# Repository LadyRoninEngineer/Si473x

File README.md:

# Si473x
Data Supporting development of Si473x series radios

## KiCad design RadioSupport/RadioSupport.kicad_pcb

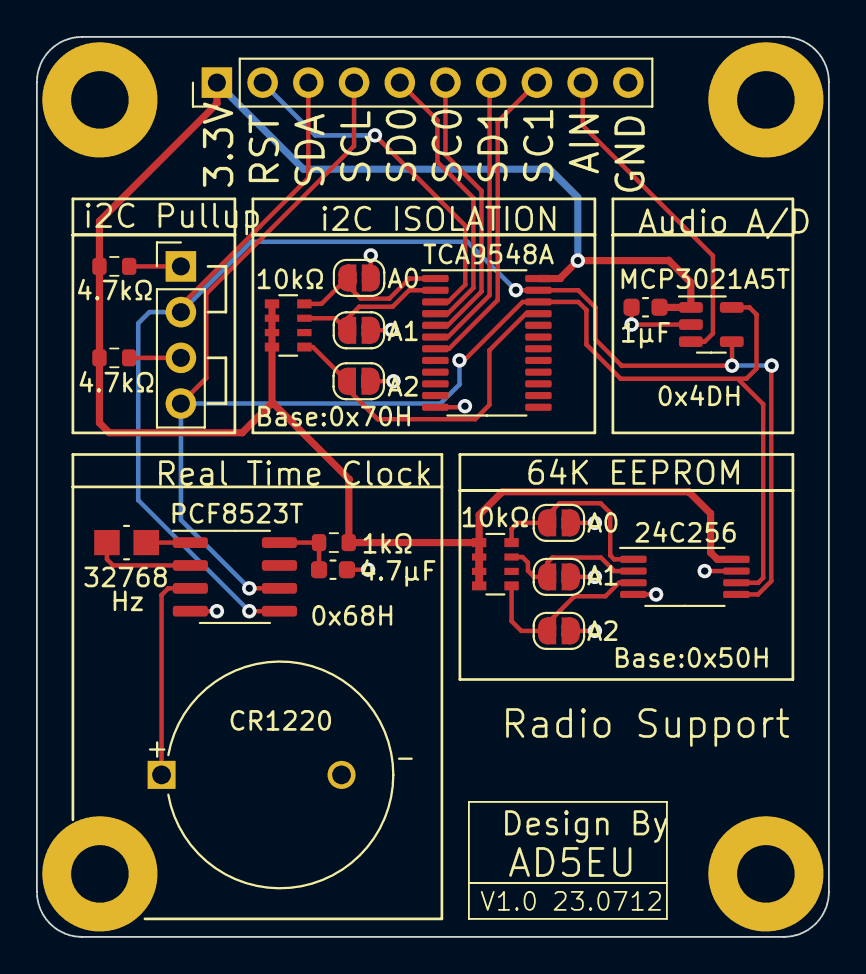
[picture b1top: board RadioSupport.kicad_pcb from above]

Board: 2 copper layers, 44.0 x 50.0 mm, 21 parts (0 on the bottom side), 22 nets.

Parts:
BT2: CR1220; BAT_BR1225A_HBN
C1: 4.7µF; C_0603_1608Metric
C2: 1µF; C_0603_1608Metric
J1: Conn_01x10_Pin; PinHeader_1x10_P2.54mm_Vertical
J2: Conn_01x04_Pin; PinHeader_1x04_P2.54mm_Vertical
JP1, JP2, JP3, JP4, JP5, JP6: Jumper_2_Bridged; SolderJumper-2_P1.3mm_Open_RoundedPad1.0x1.5mm
R1, R2: 4.7kΩ; R_0603_1608Metric
R3: 1kΩ; R_0603_1608Metric
RN1, RN2: 10kΩ; R_Array_Convex_4x0603
U1: TCA9548A; TSSOP-24_4.4x7.8mm_P0.65mm
U2: PCF8523T; SOIC-8_3.9x4.9mm_P1.27mm
U4: MCP3021A5T; SOT-23-5
U5: 24C256; TSSOP-8_4.4x3mm_P0.65mm
Y1: 32768; RT3215-32.768-12.5-TR

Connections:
+3.3V: C2.2, J1.1, R1.2, R2.2, R3.2, RN1.1 (R1.1), RN1.2 (R2.1), RN1.3 (R3.1), RN1.4 (R4.1), RN2.1 (R1.1), RN2.2 (R2.1), RN2.3 (R3.1), RN2.4 (R4.1), U1.24 (VCC), U4.1 (VDD), U5.8 (VCC)
AUDIO: J1.9, U4.3 (AIN)
GND: BT2.2 (-), C1.2, C2.1, J1.10, JP1.2 (B), JP2.2 (B), JP3.2 (B), JP4.2 (B), JP5.2 (B), JP6.2 (B), U1.12 (GND), U2.4 (VSS), U4.2 (VSS), U5.4 (GND), U5.7 (WP)
unnamed: BT2.1 (+), U2.3 (VBAT)
unnamed: J2.1, R2.1
unnamed: J2.3, R1.1
unnamed: JP1.1 (A), RN1.8 (R1.2), U1.1 (A0)
unnamed: JP2.1 (A), RN1.7 (R2.2), U1.2 (A1)
unnamed: JP3.1 (A), RN1.5 (R4.2), U1.21 (A2)
unnamed: JP4.1 (A), RN2.5 (R4.2), U5.3 (A2)
unnamed: JP5.1 (A), RN2.7 (R2.2), U5.2 (A1)
unnamed: JP6.1 (A), RN2.8 (R1.2), U5.1 (A0)
unnamed: U2.1 (OSCI), Y1.1
unnamed: U2.2 (OSCO), Y1.2
unnamed: C1.1, R3.1, U2.8 (VDD)
SCL: J1.4, J2.4, U1.22 (SCL), U2.6 (SCL), U4.5 (SCL), U5.6 (SCL)
SCL0: J1.6, U1.5 (SC0)
SCL1: J1.8, U1.7 (SC1)
SDA: J1.3, J2.2, U1.23 (SDA), U2.5 (SDA), U4.4 (SDA), U5.5 (SDA)
SDA0: J1.5, U1.4 (SD0)
SDA1: J1.7, U1.6 (SD1)
~RST: J1.2, U1.3 (~RESET)

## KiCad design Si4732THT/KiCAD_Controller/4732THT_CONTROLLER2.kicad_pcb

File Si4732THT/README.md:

Si4732 Through Hole Technology Radio
Developed By Nancy Gail Daniels - AD5EU

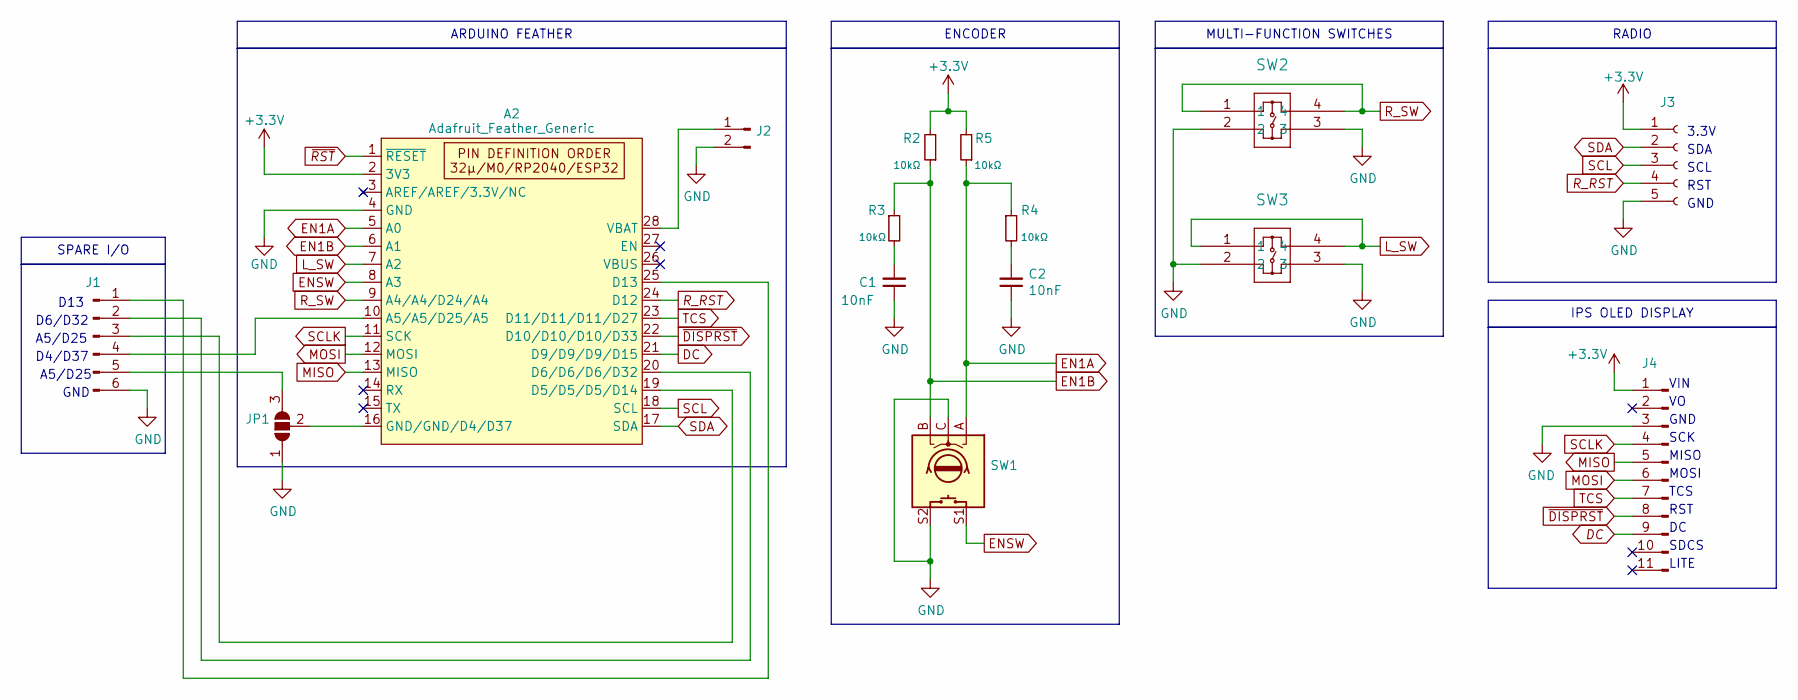
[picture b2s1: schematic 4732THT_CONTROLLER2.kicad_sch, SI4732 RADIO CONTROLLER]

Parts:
A2: Adafruit_Feather_Generic; Adafruit_Feather_WithMountingHoles
C1, C2: 10nF; C_Disc_D3.0mm_W1.6mm_P2.50mm; Mfr # C315C103K5R5TA; Digikey 399-4148-ND
J1: Conn_01x06_Pin; PinHeader_1x06_P2.54mm_Vertical
J2: Conn_01x02_Pin; JST_PH_S2B-PH-K_1x02_P2.00mm_Horizontal
J3: Conn_01x05_Socket; PinSocket_1x05_P2.54mm_Vertical
J4: Conn_01x11_Male; Display
JP1: SolderJumper_3_Open; SolderJumper-3_P1.3mm_Open_RoundedPad1.0x1.5mm
R2: 10kΩ; R_Axial_DIN0207_L6.3mm_D2.5mm_P7.62mm_Horizontal; Mfr # CFR-25JR-52-10K
R3, R4: 10kΩ; R_Axial_DIN0207_L6.3mm_D2.5mm_P7.62mm_Horizontal; Mfr # CFR-25JR-52-10K; Digikey 3-CFR-25JR-52-10KCT-ND
R5: 10kΩ; R_Axial_DIN0207_L6.3mm_D2.5mm_P7.62mm_Horizontal; Mfr # CFR-25JR-52-10K; Digikey 13-CFR-25JR-52-10KCT-ND
SW1: RotaryEncoder_Switch; RotaryEncoder_Alps_EC11E-Switch_Vertical_H20mm
SW2, SW3: D6R90F1LFS; D6R_CNK; Mfr # D6R90 F1 LFS; Digikey 401-1978-ND

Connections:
+3.3V: A2.2 (3V3), J3.1, J4.1, R2.2, R5.2
DC: A2.21 (D9/D9/D9/D15), J4.9
EN1A: A2.5 (A0), R4.1, R5.1, SW1.A
EN1B: A2.6 (A1), R2.1, R3.1, SW1.B
ENSW: A2.8 (A3), SW1.S1
GND: A2.4 (GND), C1.1, C2.1, J1.6, J2.2, J3.5, J4.3, JP1.1 (A), SW1.C, SW1.S2, SW2.2, SW2.3, SW3.2, SW3.3
L_SW: A2.7 (A2), SW3.1, SW3.4
MISO: A2.13 (MISO), J4.5
MOSI: A2.12 (MOSI), J4.6
unnamed: A2.10 (A5/A5/D25/A5), J1.4
unnamed: A2.19 (D5/D5/D5/D14), J1.3
unnamed: A2.20 (D6/D6/D6/D32), J1.2
unnamed: A2.25 (D13), J1.1
unnamed: A2.16 (GND/GND/D4/D37), JP1.2 (C)
unnamed: A2.28 (VBAT), J2.1
unnamed: C1.2, R3.2
unnamed: C2.2, R4.2
unnamed: J1.5, JP1.3 (B)
R_RST: A2.24 (D12), J3.4
R_SW: A2.9 (A4/A4/D24/A4), SW2.1, SW2.4
SCL: A2.18 (SCL), J3.3
SCLK: A2.11 (SCK), J4.4
SDA: A2.17 (SDA), J3.2
TCS: A2.23 (D11/D11/D11/D27), J4.7
~DISPRST: A2.22 (D10/D10/D10/D33), J4.8
~RST: A2.1 (~RESET)

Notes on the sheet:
RADIO
IPS OLED DISPLAY
MULTI-FUNCTION SWITCHES
ARDUINO FEATHER
SPARE I/O
ENCODER
SCL
SDCS
SDA
SCK
A5/D25
RST
VIN
TCS
LITE
MISO
MOSI
GND
3.3V
D4/D37
D6/D32
D13

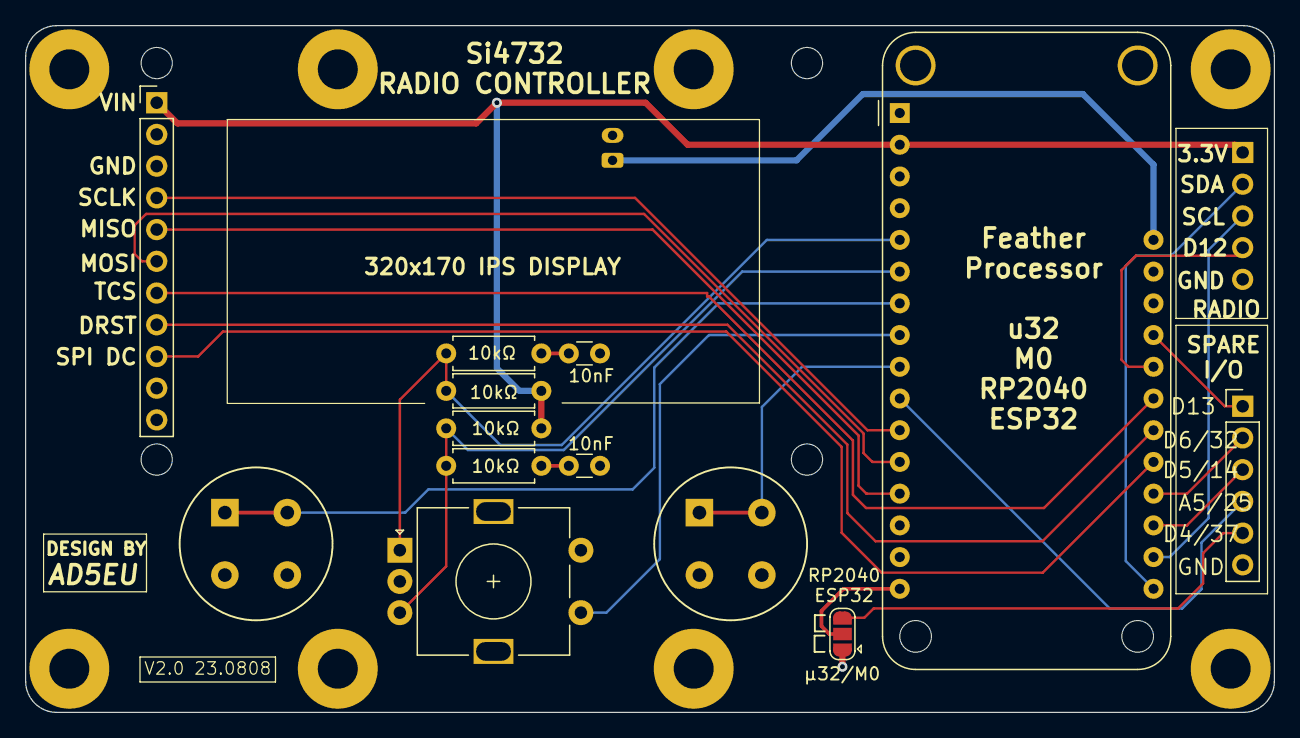
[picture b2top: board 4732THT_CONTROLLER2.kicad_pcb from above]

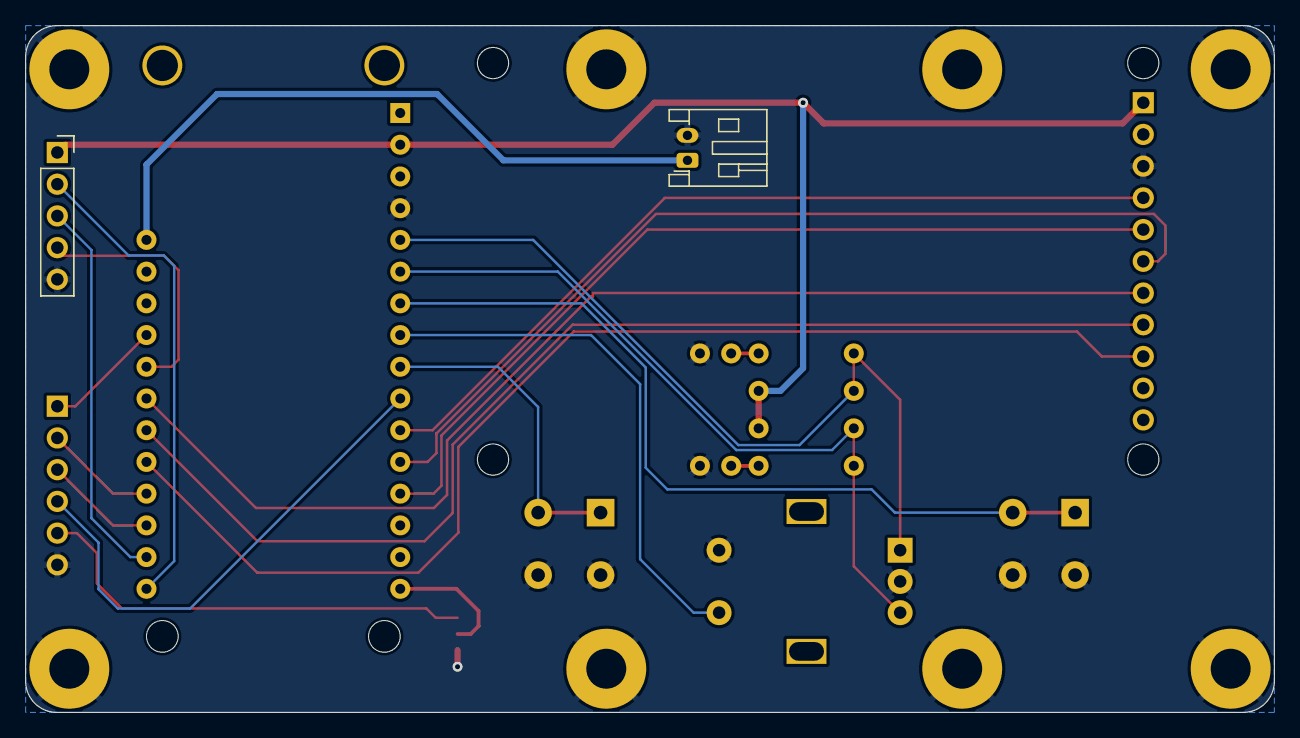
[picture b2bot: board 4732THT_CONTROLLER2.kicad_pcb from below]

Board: 2 copper layers, 100.0 x 55.0 mm, 15 parts (2 on the bottom side), 25 nets.

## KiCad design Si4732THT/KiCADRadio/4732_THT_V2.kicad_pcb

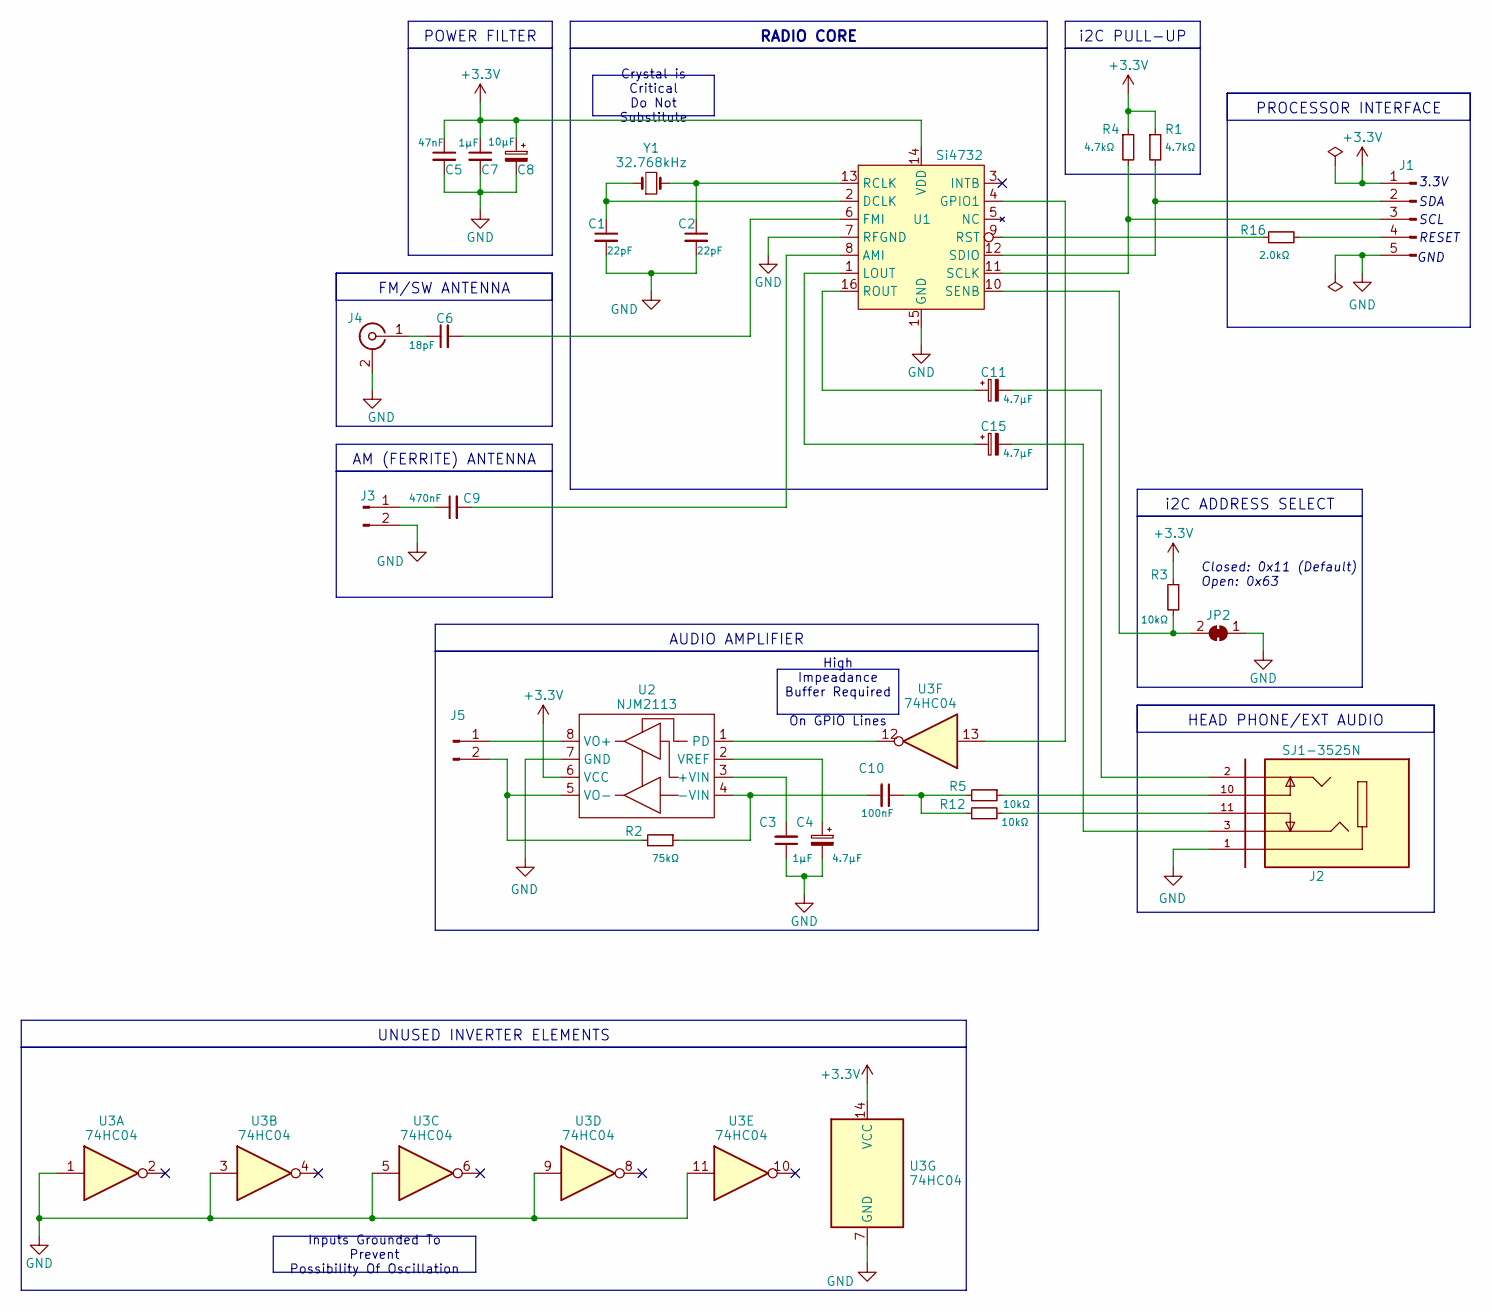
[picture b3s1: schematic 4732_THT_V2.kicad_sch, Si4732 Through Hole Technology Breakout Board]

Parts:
C1, C2: 22pF; C_Disc_D3.8mm_W2.6mm_P2.50mm
C3, C7: 1µF; CAP_C410C_AX_X7R_AXIMAX_KEM
C4, C11, C15: 4.7µF; CAPPRD250W45D400H500
C5: 47nF; C_Disc_D3.8mm_W2.6mm_P2.50mm
C6: 18pF; C_Disc_D3.8mm_W2.6mm_P2.50mm
C8: 10µF; CP_Radial_D4.0mm_P1.50mm
C9: 470nF; C_Disc_D3.8mm_W2.6mm_P2.50mm
C10: 100nF; C_Disc_D3.8mm_W2.6mm_P2.50mm
J1: Conn_01x05_Pin; PinHeader_1x05_P2.54mm_Vertical
J2: SJ1-3525N; CUI_SJ1-3525N; PARTREV 1.02
J3, J5: Conn_01x02_Pin; 1725656
J4: Conn_01x01_Female; SMA_Molex_73251-1153_EdgeMount_Horizontal
JP2: SolderJumper_2_Open; SolderJumper-2_P1.3mm_Bridged_RoundedPad1.0x1.5mm
R1, R4: 4.7kΩ; R_Axial_DIN0207_L6.3mm_D2.5mm_P7.62mm_Horizontal
R2: 75kΩ; R_Axial_DIN0207_L6.3mm_D2.5mm_P7.62mm_Horizontal
R3, R5, R12: 10kΩ; R_Axial_DIN0207_L6.3mm_D2.5mm_P7.62mm_Horizontal
R16: 2.0kΩ; R_Axial_DIN0207_L6.3mm_D2.5mm_P7.62mm_Horizontal
U1: Si4732; SOIC-16_3.9x9.9mm_P1.27mm
U2: NJM2113; DIP-8_W7.62mm
U3: 74HC04; DIP-14_W7.62mm
Y1: 32.768kHz; XTAL_ECS-.327-12.5-8X-C; Tolerance 20ppm; Mfr # ECS-.327-12.5-8X; Digikey X1123-ND

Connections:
+3.3V: C5.1, C7.1, C8.1, J1.1, R1.1, R3.1, R4.1, U1.14 (VDD), U2.6 (VCC), U3.14 (VCC)
GND: C1.2, C2.2, C3.1, C4.2, C5.2, C7.2, C8.2, J1.5, J2.1, J3.2, J4.2 (Ext), JP2.1 (A), U1.7 (RFGND), U1.15 (GND), U2.7 (GND), U3.1, U3.3, U3.5, U3.7 (GND), U3.9, U3.11
unnamed: C10.1, R5.2, R12.1
unnamed: C11.2, J2.2
unnamed: C15.2, J2.3
unnamed: J1.2, R4.2, U1.12 (SDIO)
unnamed: J1.3, R1.2, U1.11 (SCLK)
unnamed: J1.4, R16.2
unnamed: J2.10, R5.1
unnamed: J2.11, R12.2
unnamed: C9.1, J3.1
unnamed: C6.1, J4.1 (In)
unnamed: J5.1, U2.8 (VO+)
unnamed: J5.2, R2.2, U2.5 (VO-)
unnamed: JP2.2 (B), R3.2, U1.10 (SENB)
unnamed: C9.2, U1.8 (AMI)
unnamed: C1.1, U1.2 (DCLK), Y1.1
unnamed: C6.2, U1.6 (FMI)
unnamed: U1.4 (GPIO1), U3.13
unnamed: C15.1, U1.1 (LOUT)
unnamed: C2.1, U1.13 (RCLK), Y1.2
unnamed: C11.1, U1.16 (ROUT)
unnamed: R16.1, U1.9 (RST)
unnamed: C3.2, U2.3 (+VIN)
unnamed: C10.2, R2.1, U2.4 (-VIN)
unnamed: U2.1 (PD), U3.12
unnamed: C4.1, U2.2 (VREF)

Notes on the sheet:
POWER FILTER
Inputs Grounded To Prevent Possibility Of Oscillation
UNUSED INVERTER ELEMENTS
HEAD PHONE/EXT AUDIO
FM/SW ANTENNA
AUDIO AMPLIFIER
i2C ADDRESS SELECT
High Impeadance Buffer Required On GPIO Lines
AM (FERRITE) ANTENNA
i2C PULL-UP
RADIO CORE
PROCESSOR INTERFACE
Crystal is Critical Do Not Substitute
SCL
Closed: 0x11 (Default) Open: 0x63
SDA
GND
3.3V
RESET

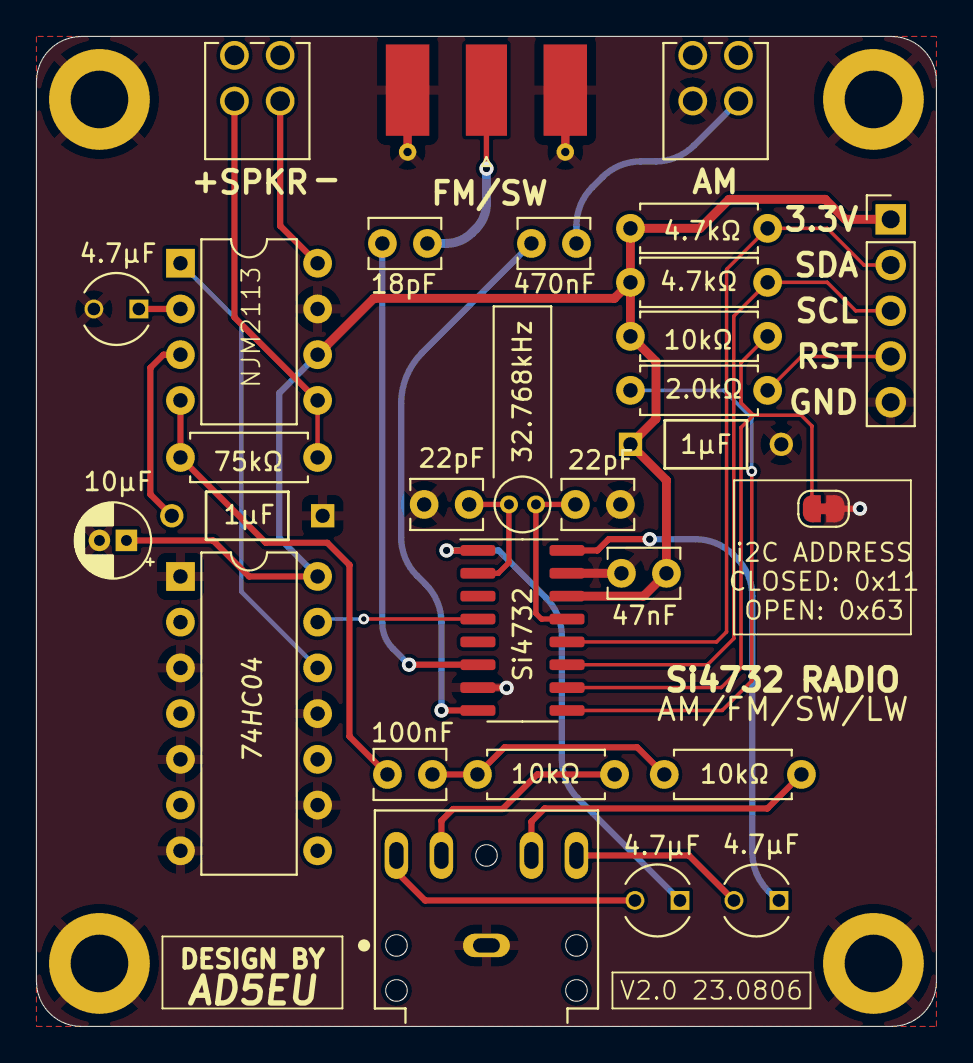
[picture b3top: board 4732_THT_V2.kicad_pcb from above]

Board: 2 copper layers, 50.0 x 55.0 mm, 29 parts (0 on the bottom side), 27 nets.

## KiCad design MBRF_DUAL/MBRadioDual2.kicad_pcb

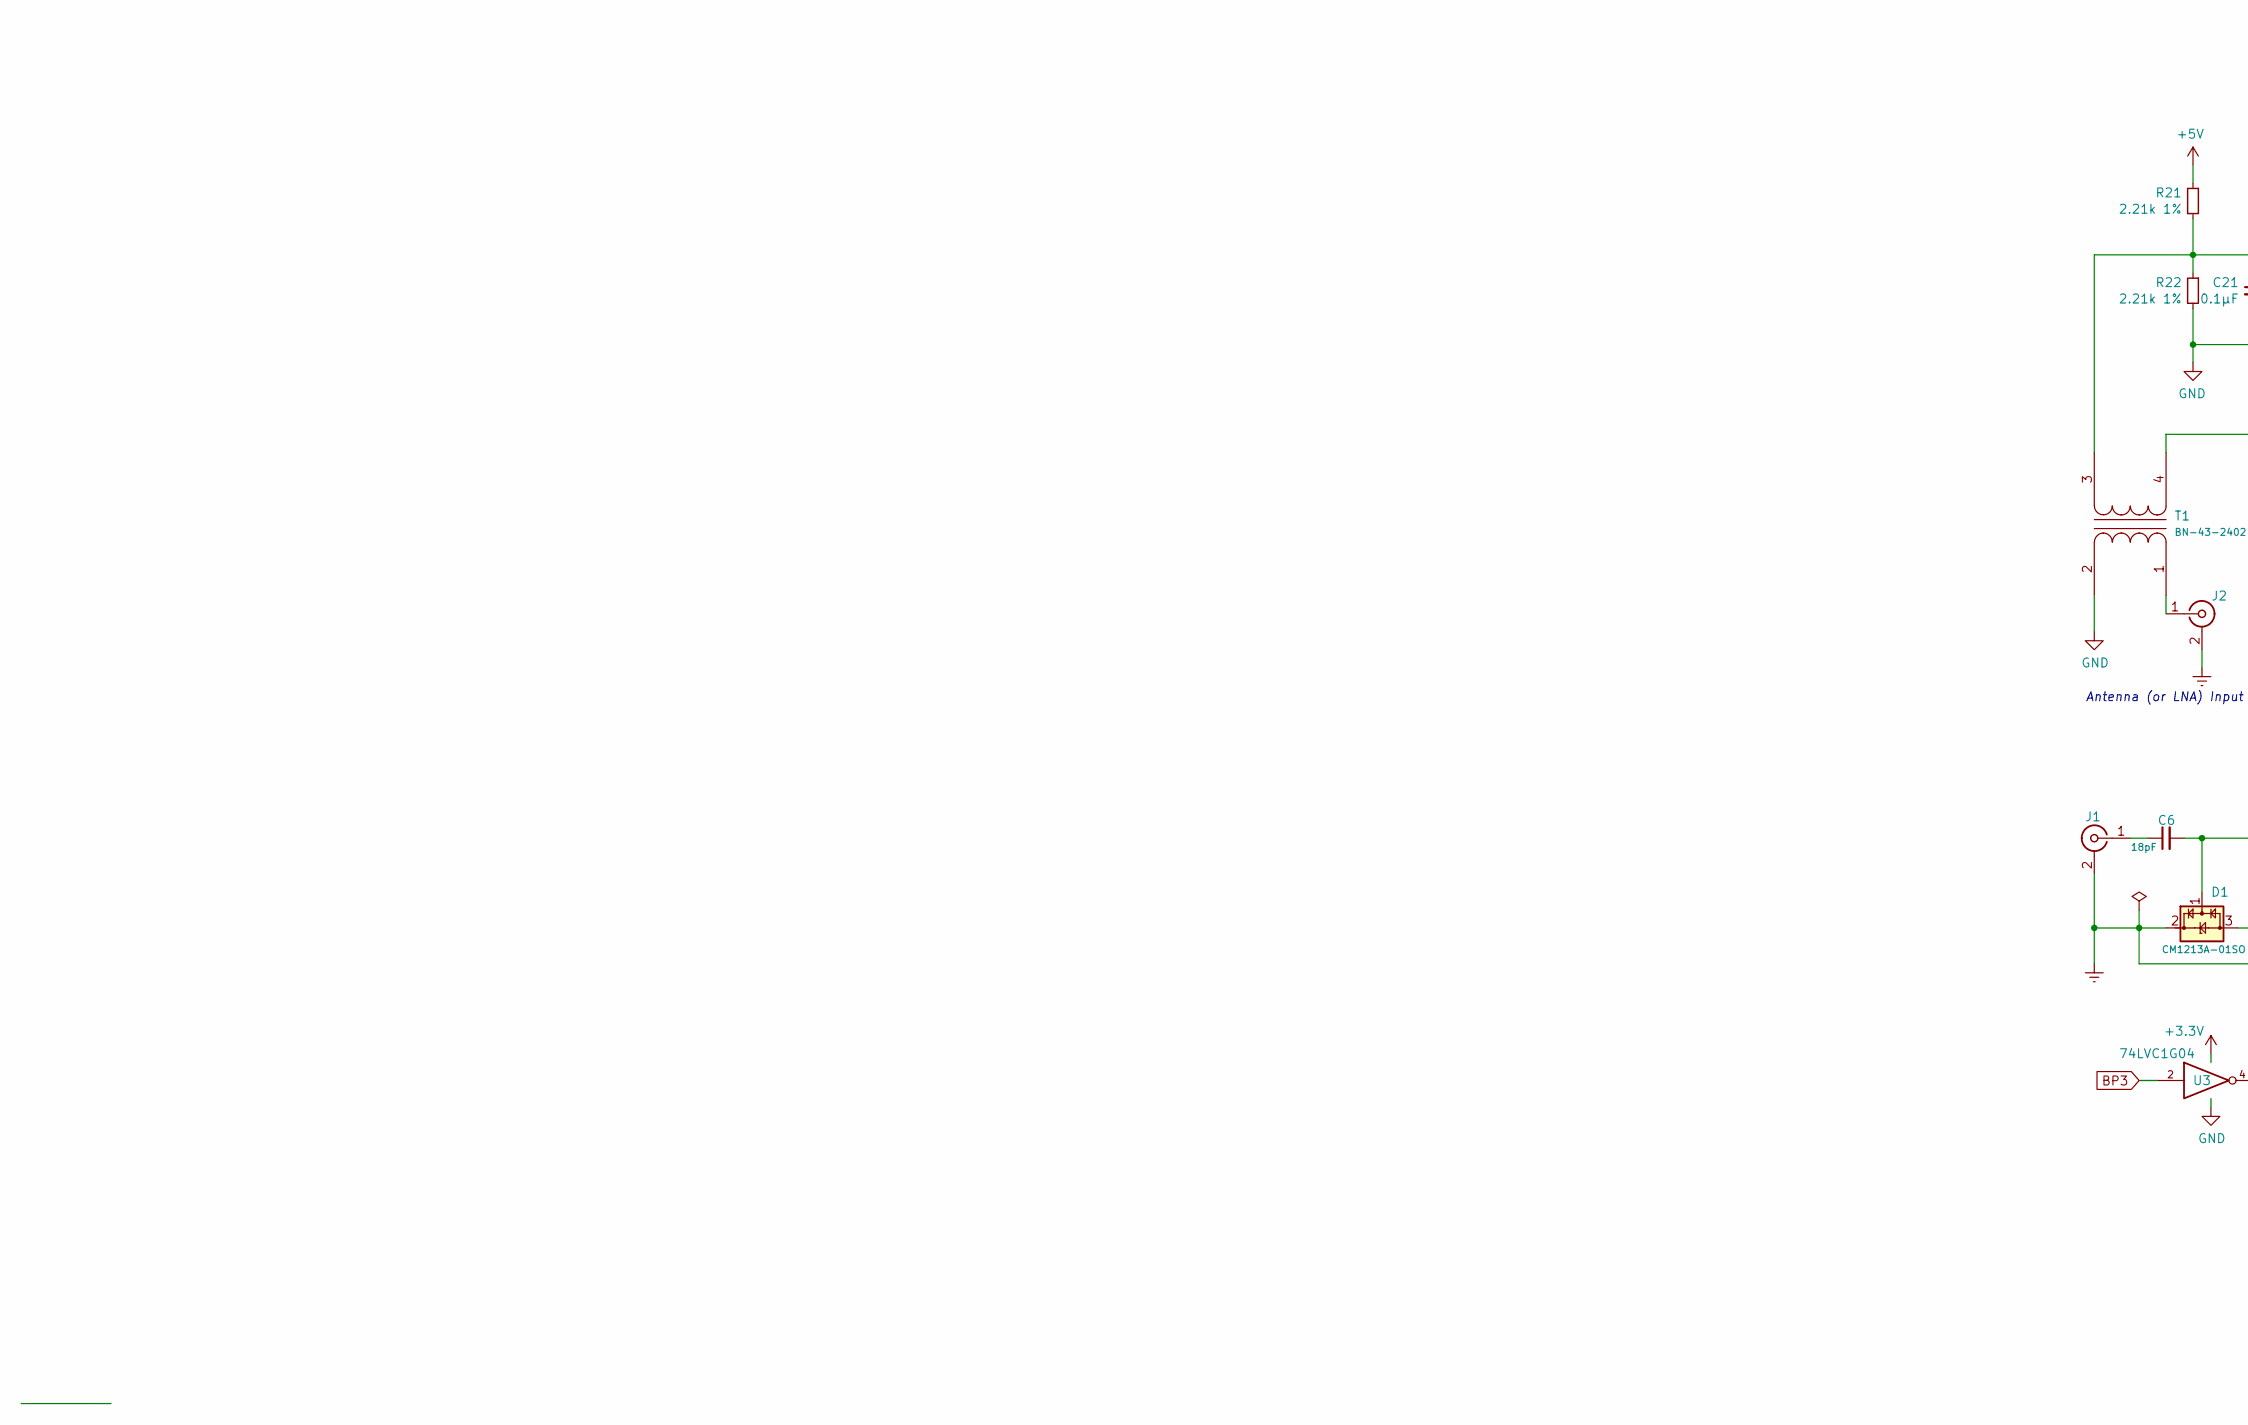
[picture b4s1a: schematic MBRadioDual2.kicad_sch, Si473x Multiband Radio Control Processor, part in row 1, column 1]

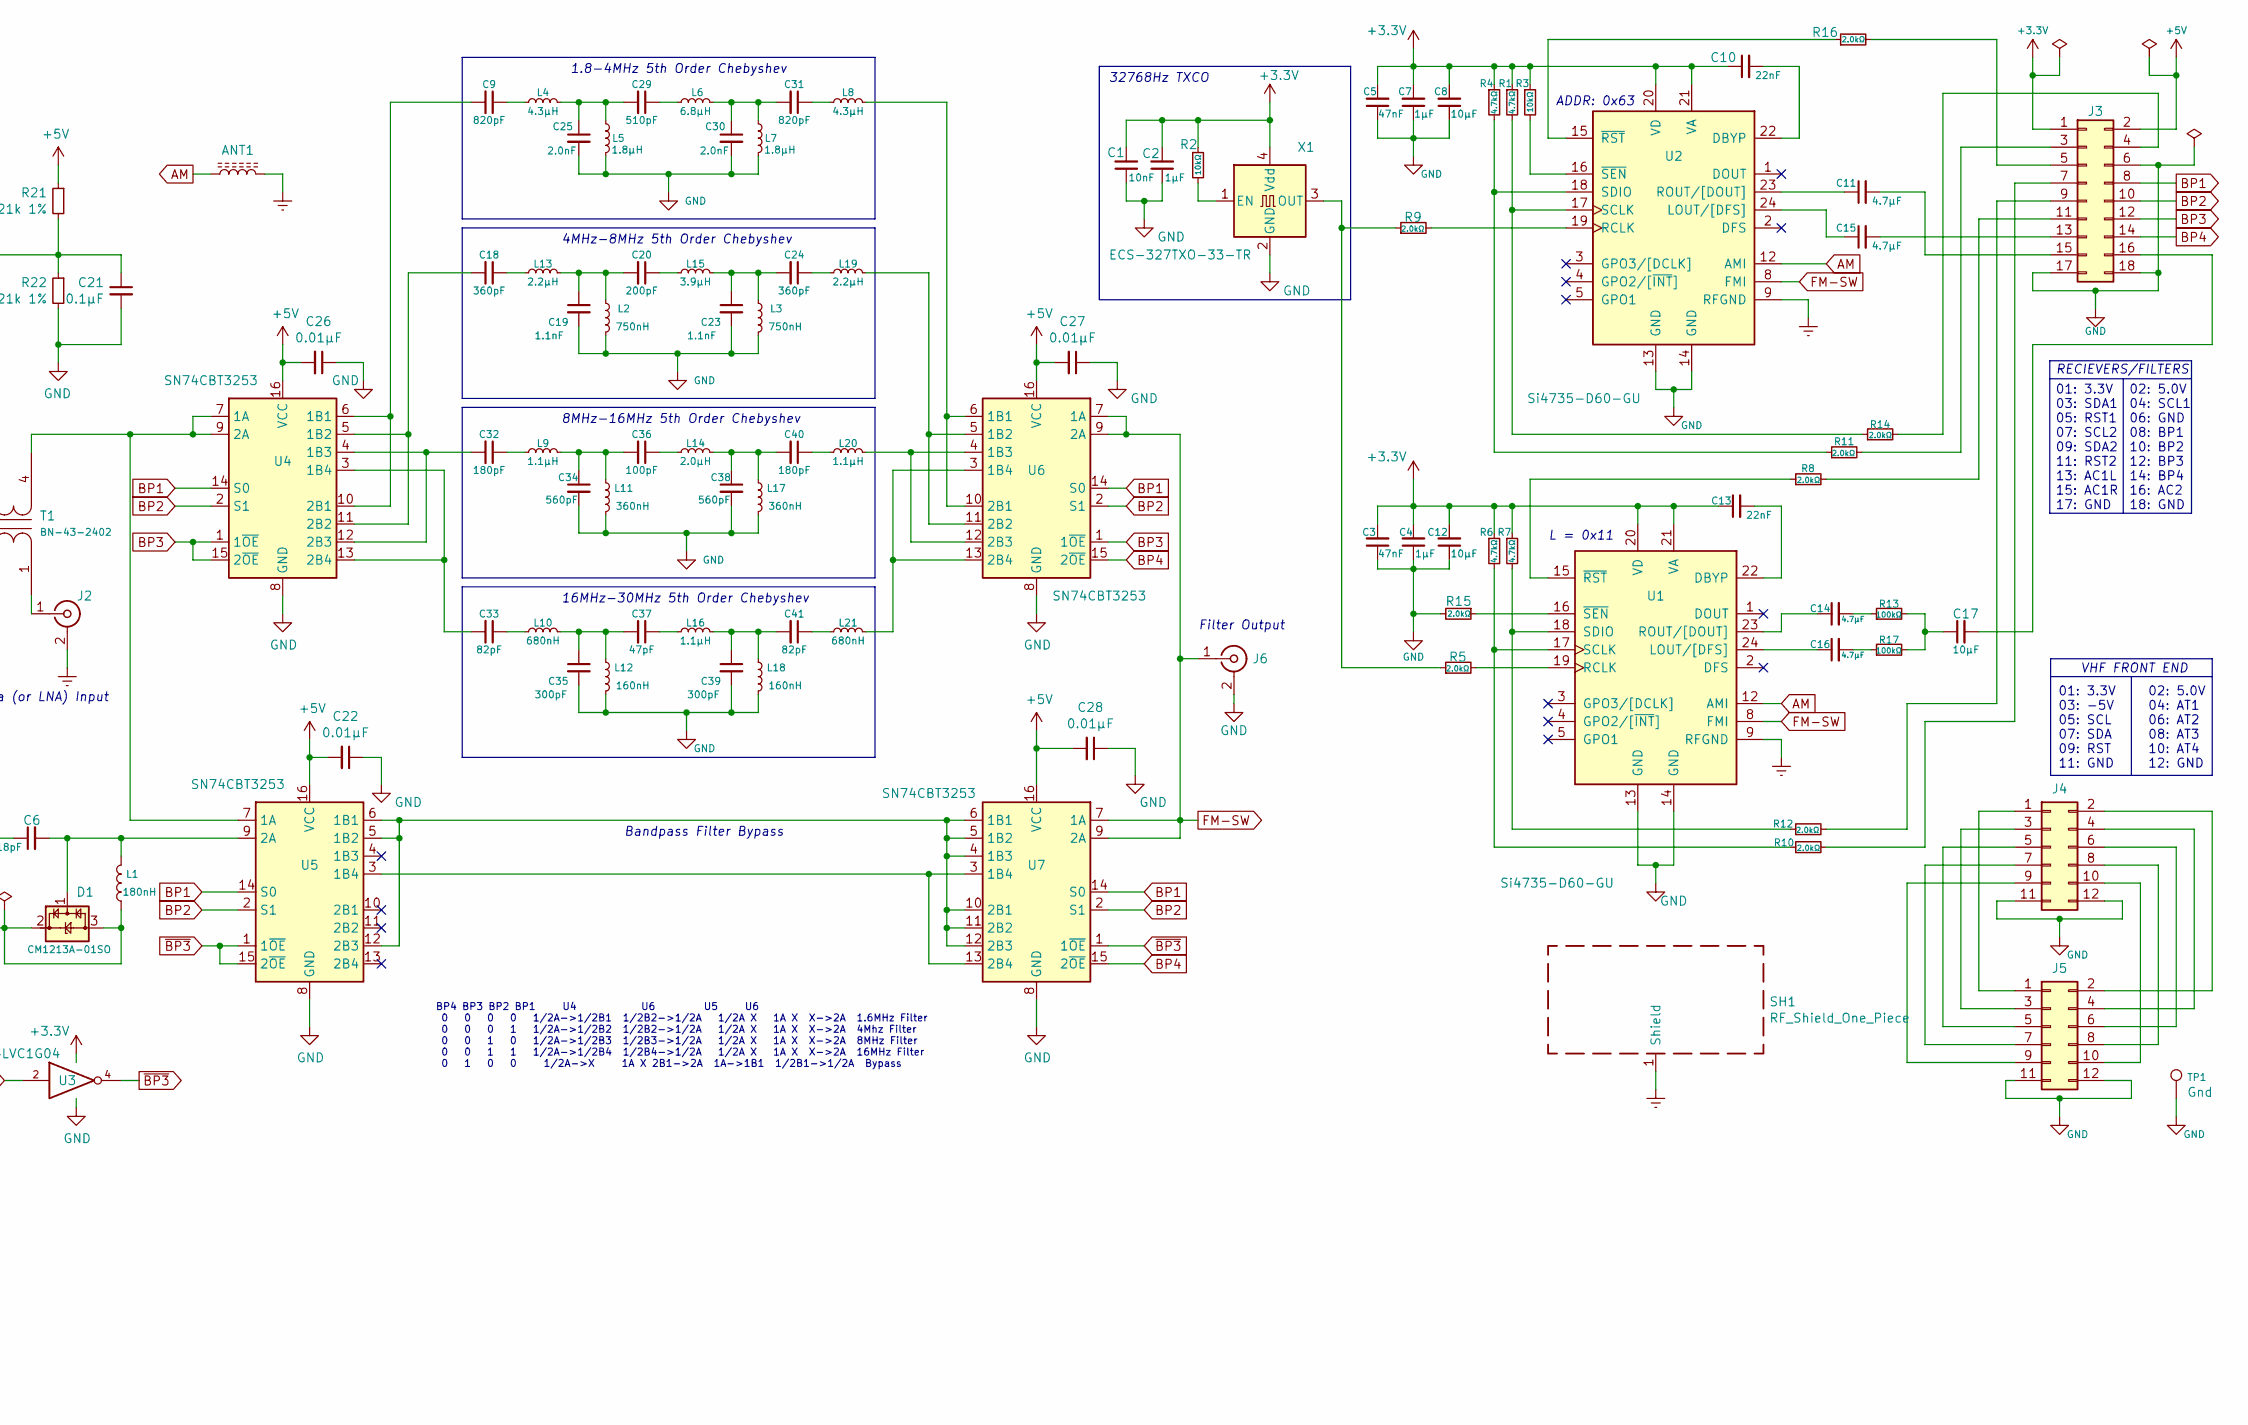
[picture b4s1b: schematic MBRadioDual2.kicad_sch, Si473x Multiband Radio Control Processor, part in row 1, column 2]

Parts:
ANT1: L_Core_Ferrite
C1: 10nF; C_0402_1005Metric
C2: 1µF; C_0402_1005Metric
C3, C5: 47nF; C_0402_1005Metric
C4, C7: 1µF; C_0603_1608Metric
C6: 18pF; C_0603_1608Metric; Tolerance 5%; Mfr # 06035U180JAT2A; Digikey 478-11831-1-ND
C8, C12, C17: 10µF; C_0603_1608Metric
C9, C31: 820pF; C_0805_2012Metric; Tolerance ±5%; Mfr # VJ0805D821JXJQJHT; Digikey 720-VJ0805D821JXJQJHTCT-ND
C10, C13: 22nF; C_0603_1608Metric
C11, C14, C15, C16: 4.7µF; C_0603_1608Metric
C18, C24: 360pF; C_0603_1608Metric; Tolerance ±2%; Mfr # C0603C361G5GAC7867; Digikey 399-14514-1-ND
C19, C23: 1.1nF; C_0805_2012Metric; Mfr # C0805C112J5GAC7800; Digikey 399-14552-1-ND
C20: 200pF; C_0805_2012Metric; Tolerance ±10%; Mfr # VJ0805D201KXPAJ; Digikey 720-1346-1-ND
C21: 0.1µF; C_0603_1608Metric
C22, C26, C27, C28: 0.01µF; C_0402_1005Metric
C25, C30: 2.0nF; C_0805_2012Metric; Tolerance ±5%; Mfr # C0805C202J5GAC7800; Digikey 399-15025-1-ND
C29: 510pF; C_0603_1608Metric; Mfr # C0603C511J5GAC7867; Digikey 399-C0603C511J5GAC7867CT-ND
C32, C40: 180pF; C_0603_1608Metric; Tolerance 10%; Mfr # VJ0603D181KXAAJ; Digikey 20-1328-1-ND
C33, C41: 82pF; C_0603_1608Metric; Tolerance 1%; Mfr # CBR06C820F5GAC; Digikey 399-16259-1-ND
C34, C38: 560pF; C_0805_2012Metric; Tolerance 10%; Mfr # VJ0805D561KXBAJ; Digikey 720-1354-1-ND
C35, C39: 300pF; C_0603_1608Metric; Tolerance 10%; Mfr # VJ0603D301KXAAJ; Digikey 720-1332-1-ND
C36: 100pF; C_0402_1005Metric; Tolerance 1%; Mfr # CBR04C101F3GAC; Digikey 399-11246-1-ND
C37: 47pF; C_0402_1005Metric; Tolerance 1%; Mfr # CBR04C470F3GAC; Digikey 399-17536-1-ND
D1: CM1213A-01SO; SOT-23; Mfr # CM1213A-01SO; Digikey CM1213A-01SOOSCT-ND
J1, J2, J6: Conn_01x01_Female; SMA_Amphenol_132134-10_Vertical
J3: Conn_02x09_Odd_Even; PinHeader_2x09_P2.54mm_Vertical
J4, J5: Conn_02x06_Odd_Even; PinHeader_2x06_P2.54mm_Vertical
L1: 180nH; L_0603_1608Metric; Mfr # LQW18ANR18J00D; Digikey 490-6928-1-ND
L2, L3: 750nH; L_1008_2520Metric; Tolerance 5%; Mfr # 1008CS-751XJLC; Mouser 994-1008CS-751XJLC
L4: 4.3µH; L_Toroid_Vertical_Amidon_T30-2; Tolerance 32 turns
L5, L7: 1.8µH; L_1008_2520Metric; Tolerance 2%; Mfr # LQW2UAS1R8G0CL; Mouser 81-LQW2UAS1R8G0CL
L6: 6.8µH; L_Toroid_Vertical_Amidon_T30-2; Tolerance 40 turns
L8: 4.3µH; L_Toroid_Vertical_Amidon_T30-2
L9, L16, L20: 1.1µH; L_Toroid_Vertical_Amidon_T25-6
L10, L21: 680nH; L_0805_2012Metric; Tolerance 5%; Mfr # 0805HP-681XJRC; Mouser 994-0805HP-681XJRC
L11, L17: 360nH; L_0603_1608Metric; Tolerance 2%; Mfr # 0603HP-R36XGLW; Mouser 994-0603HP-R36XGLW
L12, L18: 160nH; L_0805_2012Metric; Tolerance 2%; Mfr # 0805HP-151XGRC; Mouser 994-0805HP-151XGRC
L13, L19: 2.2µH; L_Toroid_Vertical_Amidon_T25-6
L14: 2.0µH; L_Toroid_Vertical_Amidon_T25-6
L15: 3.9µH; L_Toroid_Vertical_Amidon_T25-6
R1, R4, R6, R7: 4.7kΩ; R_0603_1608Metric
R2, R3: 10kΩ; R_0603_1608Metric
R5, R8, R9, R10, R11, R12, R14, R15, R16: 2.0kΩ; R_0603_1608Metric
R13, R17: 100kΩ; R_0603_1608Metric
R21, R22: 2.21k 1%; R_0603_1608Metric
SH1: RF_Shield_One_Piece; Laird_Technologies_BMI-S-203-F_26.21x26.21mm
T1: BN-43-2402; BN43-2402
TP1: Gnd; TestPoint_Keystone_5000-5004_Miniature
U1, U2: Si4735-D60-GU; SSOP-24_3.9x8.7mm_P0.635mm
U3: 74LVC1G04; TSOT-23-5
U4, U5, U6, U7: SN74CBT3253; TSSOP-16_4.4x5mm_P0.65mm
X1: ECS-327TXO-33-TR; Oscillator_SMD_Abracon_ASE-4Pin_3.2x2.5mm

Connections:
+3V3: C1.2, C2.2, C3.2, C4.2, C5.2, C7.2, C8.2, C10.1, C12.2, C13.1, J3.1, R1.1, R2.1, R3.1, R4.1, R6.1, R7.1, U1.20 (VD), U1.21 (VA), U2.20 (VD), U2.21 (VA), U3.5 (VCC), X1.4 (Vdd)
+5V: C22.2, C26.2, C27.2, C28.2, J3.2, R21.1, U4.16 (VCC), U5.16 (VCC), U6.16 (VCC), U7.16 (VCC)
AM: ANT1.1, U1.12 (AMI), U2.12 (AMI)
BP1: J3.8, U4.14 (S0), U5.14 (S0), U6.14 (S0), U7.14 (S0)
BP2: J3.10, U4.2 (S1), U5.2 (S1), U6.2 (S1), U7.2 (S1)
BP3: J3.12, U3.2, U4.1 (1~OE), U4.15 (2~OE), U6.1 (1~OE)
BP4: J3.14, U6.15 (2~OE), U7.15 (2~OE)
Earth: ANT1.2, D1.2 (VP), D1.3 (VN), J1.2 (Ext), J2.2 (Ext), L1.2, SH1.1, U1.9 (RFGND), U2.9 (RFGND)
FM-SW: J6.1 (In), U1.8 (FMI), U2.8 (FMI), U6.7 (1A), U6.9 (2A), U7.7 (1A), U7.9 (2A)
GND: C1.1, C2.1, C3.1, C4.1, C5.1, C7.1, C8.1, C12.1, C19.2, C21.2, C22.1, C23.2, C25.2, C26.1, C27.1, C28.1, C30.2, C34.2, C35.2, C38.2, C39.2, J3.6, J3.17, J3.18, J4.11, J4.12, J5.11, J5.12, J6.2 (Ext), L2.2, L3.2, L5.2, L7.2, L11.2, L12.2, L17.2, L18.2, R15.2, R22.2, T1.2 (AB), TP1.1, U1.13 (GND), U1.14 (GND), U2.13 (GND), U2.14 (GND), U3.3 (GND), U4.8 (GND), U5.8 (GND), U6.8 (GND), U7.8 (GND), X1.2 (GND)
unnamed: C6.1, J1.1 (In)
unnamed: C6.2, D1.1 (CH1), L1.1, U5.9 (2A)
unnamed: C9.1, L4.1
unnamed: C9.2, U4.6 (1B1), U4.10 (2B1)
unnamed: C10.2, U2.22 (DBYP)
unnamed: C11.1, U2.23 (ROUT/[DOUT])
unnamed: C11.2, J3.15
unnamed: C13.2, U1.22 (DBYP)
unnamed: C14.1, U1.23 (ROUT/[DOUT])
unnamed: C14.2, R13.1
unnamed: C15.1, U2.24 (LOUT/[DFS])
unnamed: C15.2, J3.13
unnamed: C16.1, U1.24 (LOUT/[DFS])
unnamed: C16.2, R17.1
unnamed: C17.1, R13.2, R17.2
unnamed: C17.2, J3.16
unnamed: C18.1, L13.1
unnamed: C18.2, U4.5 (1B2), U4.11 (2B2)
unnamed: C19.1, C20.2, L2.1, L13.2
unnamed: C20.1, L15.1
unnamed: C21.1, R21.2, R22.1, T1.3 (SA)
unnamed: C23.1, C24.2, L3.1, L15.2
unnamed: C24.1, L19.1
unnamed: C25.1, C29.2, L4.2, L5.1
unnamed: C29.1, L6.1
unnamed: C30.1, C31.2, L6.2, L7.1
unnamed: C31.1, L8.1
unnamed: C32.1, L9.1
unnamed: C32.2, U4.4 (1B3), U4.12 (2B3)
unnamed: C33.1, L10.1
unnamed: C33.2, U4.3 (1B4), U4.13 (2B4)
unnamed: C34.1, C36.2, L9.2, L11.1
unnamed: C35.1, C37.2, L10.2, L12.1
unnamed: C36.1, L14.1
unnamed: C37.1, L16.1
unnamed: C38.1, C40.2, L14.2, L17.1
unnamed: C39.1, C41.2, L16.2, L18.1
unnamed: C40.1, L20.1
unnamed: C41.1, L21.1
unnamed: J2.1 (In), T1.1 (AA)
unnamed: J3.3, R11.2
unnamed: J3.4, R14.2
unnamed: J3.5, R16.2
unnamed: J3.7, R10.2
unnamed: J3.9, R12.2
unnamed: J3.11, R8.2
unnamed: J4.1, J5.1
unnamed: J4.2, J5.2
unnamed: J4.3, J5.3
unnamed: J4.4, J5.4
unnamed: J4.5, J5.5
unnamed: J4.6, J5.6
unnamed: J4.7, J5.7
unnamed: J4.8, J5.8
unnamed: J4.9, J5.9
unnamed: J4.10, J5.10
unnamed: L8.2, U6.6 (1B1), U6.10 (2B1)
unnamed: L19.2, U6.5 (1B2), U6.11 (2B2)
unnamed: L20.2, U6.4 (1B3), U6.12 (2B3)
unnamed: L21.2, U6.3 (1B4), U6.13 (2B4)
unnamed: R1.2, R14.1, U2.17 (SCLK)
unnamed: R2.2, X1.1 (EN)
unnamed: R3.2, U2.16 (~SEN)
unnamed: R5.1, R9.1, X1.3 (OUT)
unnamed: R5.2, U1.19 (RCLK)
unnamed: R8.1, U1.15 (~RST)
unnamed: R9.2, U2.19 (RCLK)
unnamed: R6.2, R10.1, U1.17 (SCLK)
unnamed: R4.2, R11.1, U2.18 (SDIO)
unnamed: R7.2, R12.1, U1.18 (SDIO)
unnamed: R15.1, U1.16 (~SEN)
unnamed: R16.1, U2.15 (~RST)
unnamed: T1.4 (SB), U4.7 (1A), U4.9 (2A), U5.7 (1A)
unnamed: U5.3 (1B4), U7.3 (1B4), U7.13 (2B4)
unnamed: U5.5 (1B2), U5.6 (1B1), U5.12 (2B3), U7.4 (1B3), U7.5 (1B2), U7.6 (1B1), U7.10 (2B1), U7.11 (2B2), U7.12 (2B3)
~BP3: U3.4, U5.1 (1~OE), U5.15 (2~OE), U7.1 (1~OE)

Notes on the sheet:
4MHz-8MHz 5th Order Chebyshev
L = 0x11
02: 5.0V 04: SCL1 06: GND 08: BP1 10: BP2 12: BP3 14: BP4 16: AC2 18: GND
1.8-4MHz 5th Order Chebyshev
02: 5.0V 04: AT1 06: AT2 08: AT3 10: AT4 12: GND
BP4 BP3 BP2 BP1 U4 U6 U5 U6 0 0 0 0 1/2A->1/2B1 1/2B2->1/2A 1/2A X 1A X X->2A 1.6MHz Filter 0 0 0 1 1/2A->1/2B2 1/2B2->1/2A 1/2A X 1A X X->2A 4Mhz Filter 0 0 1 0 1/2A->1/2B3 1/2B3->1/2A 1/2A X 1A X X->2A 8MHz Filter 0 0 1 1 1/2A->1/2B4 1/2B4->1/2A 1/2A X 1A X X->2A 16MHz Filter 0 1 0 0 1/2A->X 1A X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
01: 3.3V 03: -5V 05: SCL 07: SDA 09: RST 11: GND
01: 3.3V 03: SDA1 05: RST1 07: SCL2 09: SDA2 11: RST2 13: AC1L 15: AC1R 17: GND
Filter Output
ADDR: 0x63
8MHz-16MHz 5th Order Chebyshev
Bandpass Filter Bypass
RECIEVERS/FILTERS
32768Hz TXCO
16MHz-30MHz 5th Order Chebyshev
VHF FRONT END
Antenna (or LNA) Input

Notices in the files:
parts and their libraries:
Copyright 2016 Accelerated Designs. All rights reserved.
Copyright 2021 Accelerated Designs. All rights reserved.
